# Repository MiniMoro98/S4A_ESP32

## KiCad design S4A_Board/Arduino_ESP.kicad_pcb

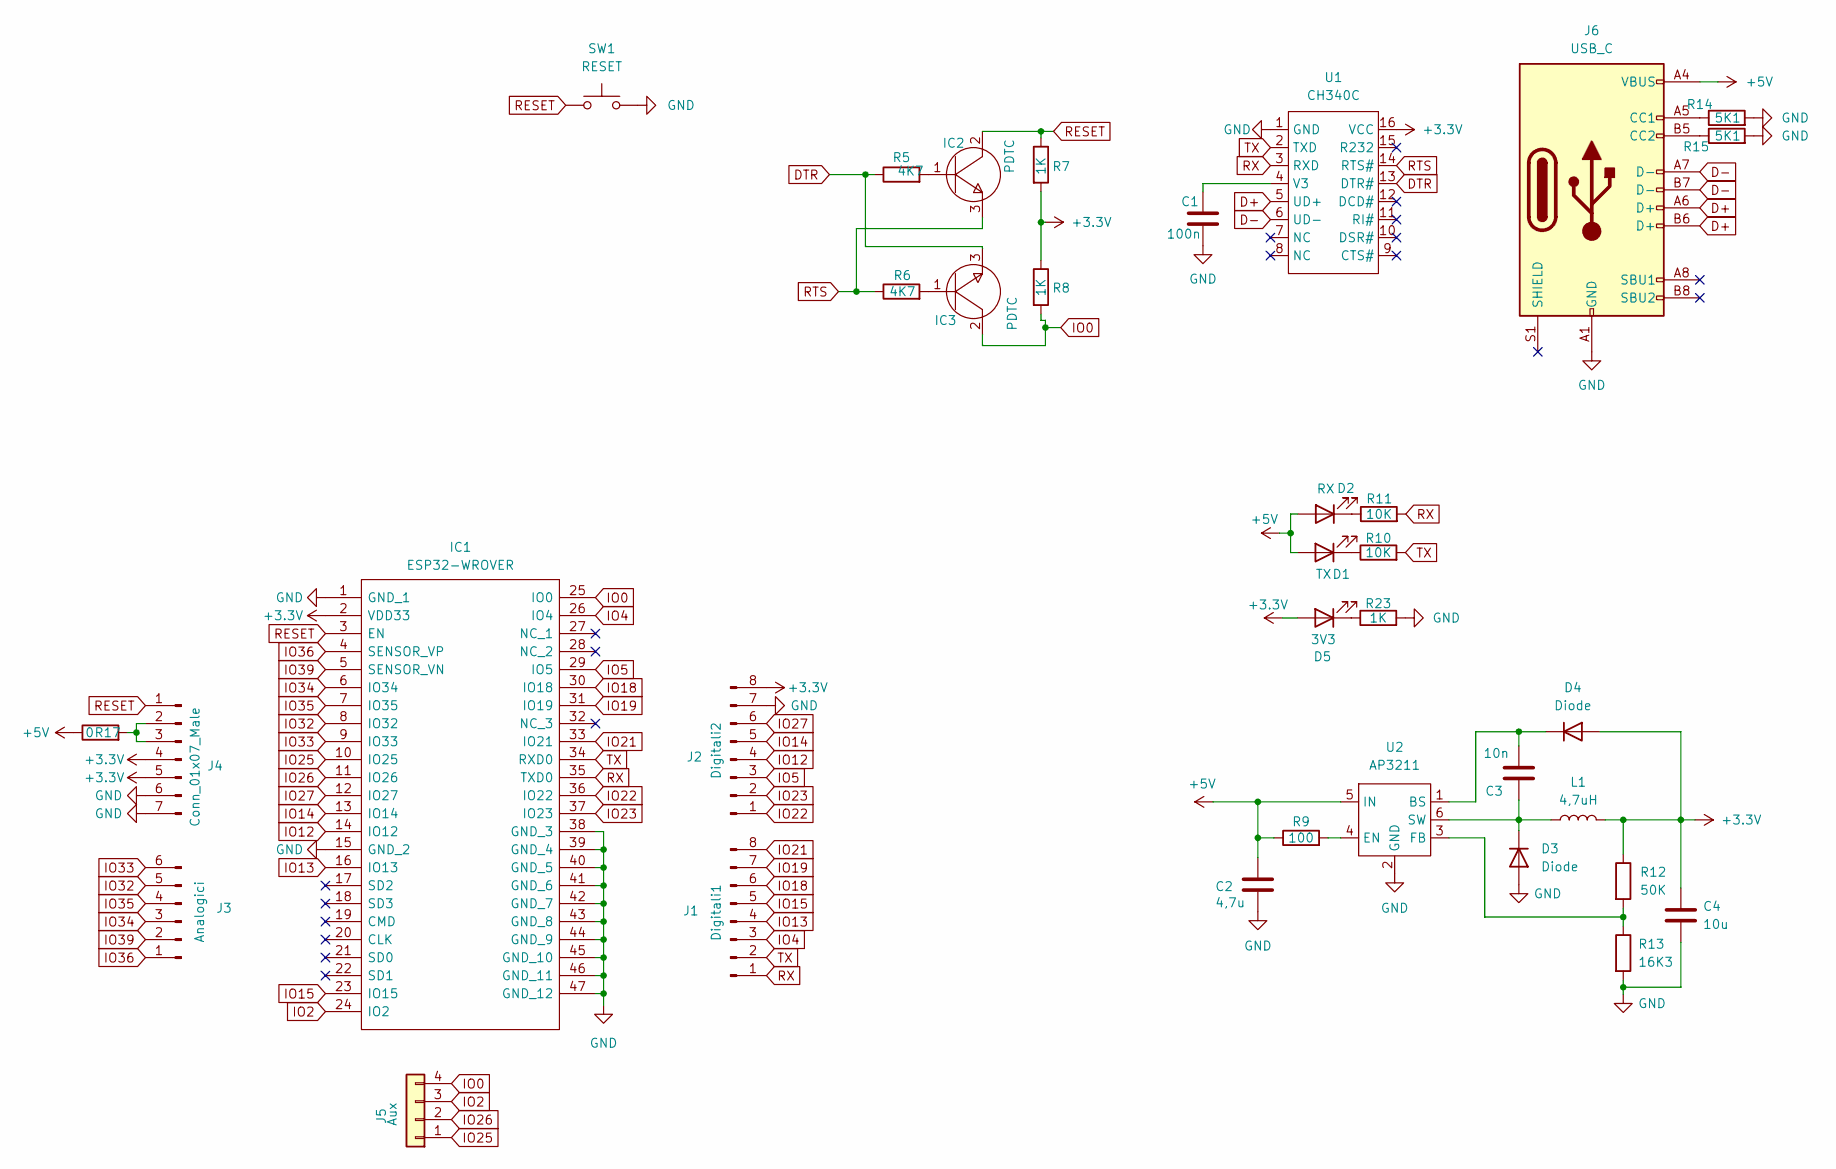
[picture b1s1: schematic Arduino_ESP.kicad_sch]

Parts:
C1: 100n; C_0603_1608Metric
C2: 4,7u; Condensatore_G
C3: 10n; Condensatore_P
C4: 10u; Condensatore_G
D1: TX; LED_0805_2012Metric
D2: RX; LED_0805_2012Metric
D3: Diode; Diodo_G
D4: Diode; Diodo_P
D5: 3V3; LED_0805_2012Metric
IC1: ESP32-WROVER; ESP32WROVERB8MB; Manufacturer_Part_Number ESP32-WROVER-B (8MB); Mouser Part Number 356-ESP32-WRO-B(8MB)
IC2, IC3: PDTC; SOT-23
J1: Digitali1; PinSocket_1x08_P2.54mm_Vertical
J2: Digitali2; PinSocket_1x08_P2.54mm_Vertical
J3: Analogici; PinSocket_1x06_P2.54mm_Vertical
J4: Conn_01x07_Male; PinSocket_1x07_P2.54mm_Vertical
J5: Aux; PinHeader_1x04_P2.54mm_Vertical
J6: USB_C; USB_C_Receptacle_HRO_TYPE-C-31-M-12
L1: 4,7uH; Induttanza
R5, R6: 4K7; R_0603_1608Metric
R7, R8, R23: 1K; R_0603_1608Metric
R9: 100; Resistenza
R10, R11: 10K; R_0603_1608Metric
R12: 50K; Resistenza
R13: 16K3; Resistenza
R14, R15: 5K1; R_0603_1608Metric
R17: 0; R_0402_1005Metric
SW1: RESET; SW_SPST_CK_RS282G05A3
U1: CH340C; SO-16_3.9x9.9mm_P1.27mm
U2: AP3211

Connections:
+3.3V: C4.1, D4.1 (A), D5.2 (A), IC1.2 (VDD33), J2.8, J4.4, J4.5, L1.2, R7.2, R8.1, R12.1, U1.16 (VCC)
+5V: C2.1, D1.2 (A), D2.2 (A), J6.A4 (VBUS), J6.A9 (VBUS), J6.B4 (VBUS), J6.B9 (VBUS), R9.1, R17.1, U2.5 (IN)
D+: J6.A6 (D+), J6.B6 (D+), U1.5 (UD+)
D-: J6.A7 (D-), J6.B7 (D-), U1.6 (UD-)
DTR: IC3.3, R5.1, U1.13 (DTR#)
GND: C1.2, C2.2, C4.2, D3.1 (A), IC1.1 (GND_1), IC1.15 (GND_2), IC1.38 (GND_3), IC1.39 (GND_4), IC1.40 (GND_5), IC1.41 (GND_6), IC1.42 (GND_7), IC1.43 (GND_8), IC1.44 (GND_9), IC1.45 (GND_10), IC1.46 (GND_11), IC1.47 (GND_12), J2.7, J4.6, J4.7, J6.A1 (GND), J6.A12 (GND), J6.B1 (GND), J6.B12 (GND), R13.2, R14.2, R15.2, R23.2, SW1.2, U1.1 (GND), U2.2 (GND)
IO0: IC1.25 (IO0), IC3.2, J5.4, R8.2
IO2: IC1.24 (IO2), J5.3
IO4: IC1.26 (IO4), J1.3
IO5: IC1.29 (IO5), J2.3
IO12: IC1.14 (IO12), J2.4
IO13: IC1.16 (IO13), J1.4
IO14: IC1.13 (IO14), J2.5
IO15: IC1.23 (IO15), J1.5
IO18: IC1.30 (IO18), J1.6
IO19: IC1.31 (IO19), J1.7
IO21: IC1.33 (IO21), J1.8
IO22: IC1.36 (IO22), J2.1
IO23: IC1.37 (IO23), J2.2
IO25: IC1.10 (IO25), J5.1
IO26: IC1.11 (IO26), J5.2
IO27: IC1.12 (IO27), J2.6
IO32: IC1.8 (IO32), J3.5
IO33: IC1.9 (IO33), J3.6
IO34: IC1.6 (IO34), J3.3
IO35: IC1.7 (IO35), J3.4
IO36: IC1.4 (SENSOR_VP), J3.1
IO39: IC1.5 (SENSOR_VN), J3.2
unnamed: D1.1 (K), R10.1
unnamed: D2.1 (K), R11.1
unnamed: C3.2, D3.2 (K), L1.1, U2.6 (SW)
unnamed: C3.1, D4.2 (K), U2.1 (BS)
unnamed: D5.1 (K), R23.1
unnamed: IC2.1, R5.2
unnamed: IC3.1, R6.2
unnamed: J4.2, J4.3, R17.2
unnamed: J6.A5 (CC1), R14.1
unnamed: J6.B5 (CC2), R15.1
unnamed: C1.1, U1.4 (V3)
unnamed: R9.2, U2.4 (EN)
unnamed: R12.2, R13.1, U2.3 (FB)
RESET: IC1.3 (EN), IC2.2, J4.1, R7.1, SW1.1
RTS: IC2.3, R6.1, U1.14 (RTS#)
RX: IC1.35 (TXD0), J1.1, R11.2, U1.3 (RXD)
TX: IC1.34 (RXD0), J1.2, R10.2, U1.2 (TXD)

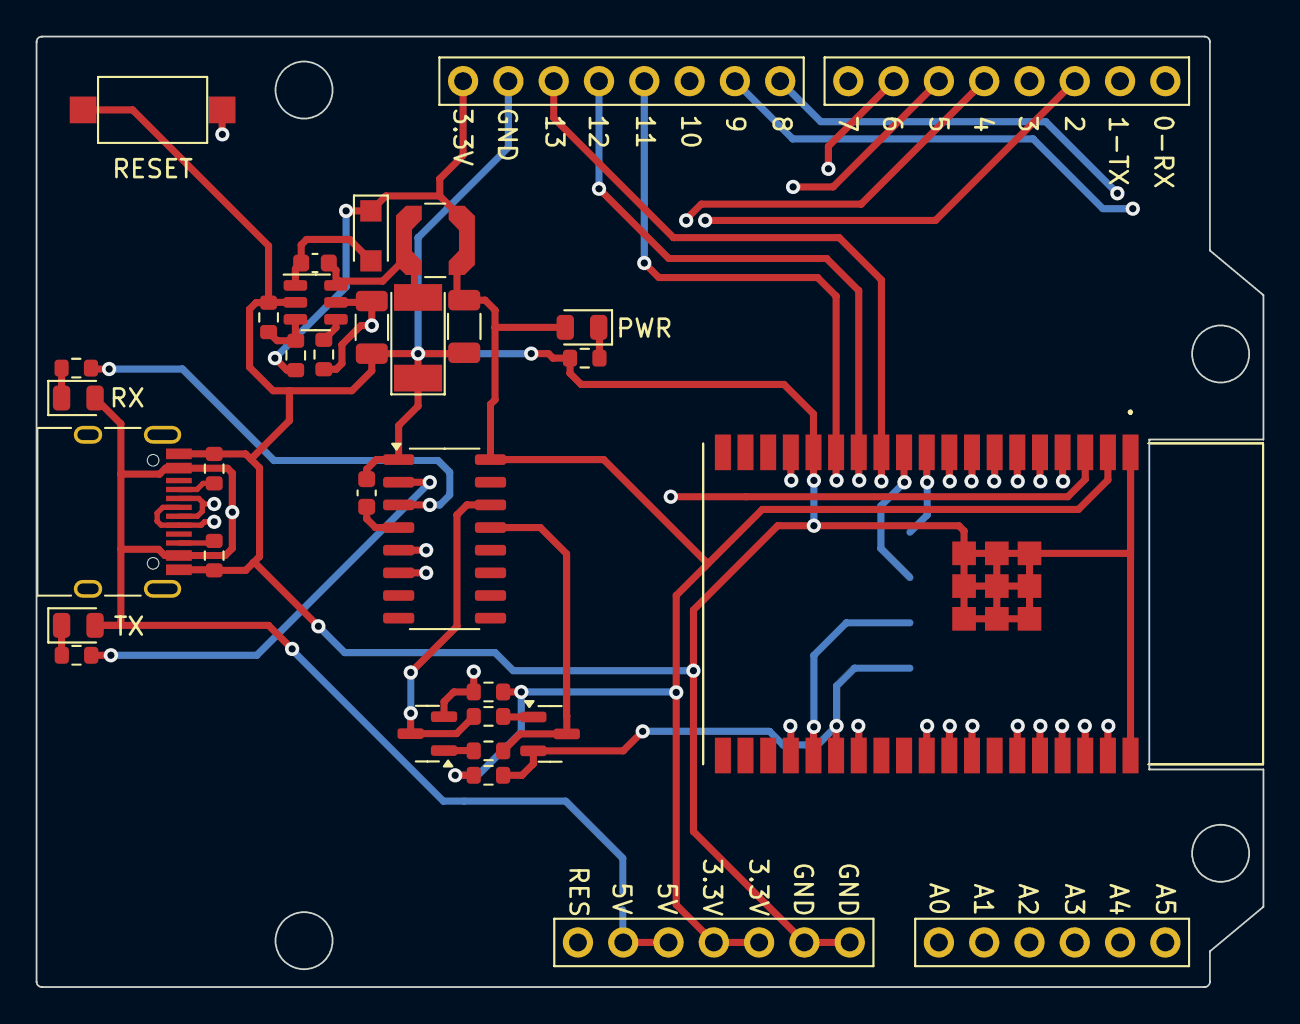
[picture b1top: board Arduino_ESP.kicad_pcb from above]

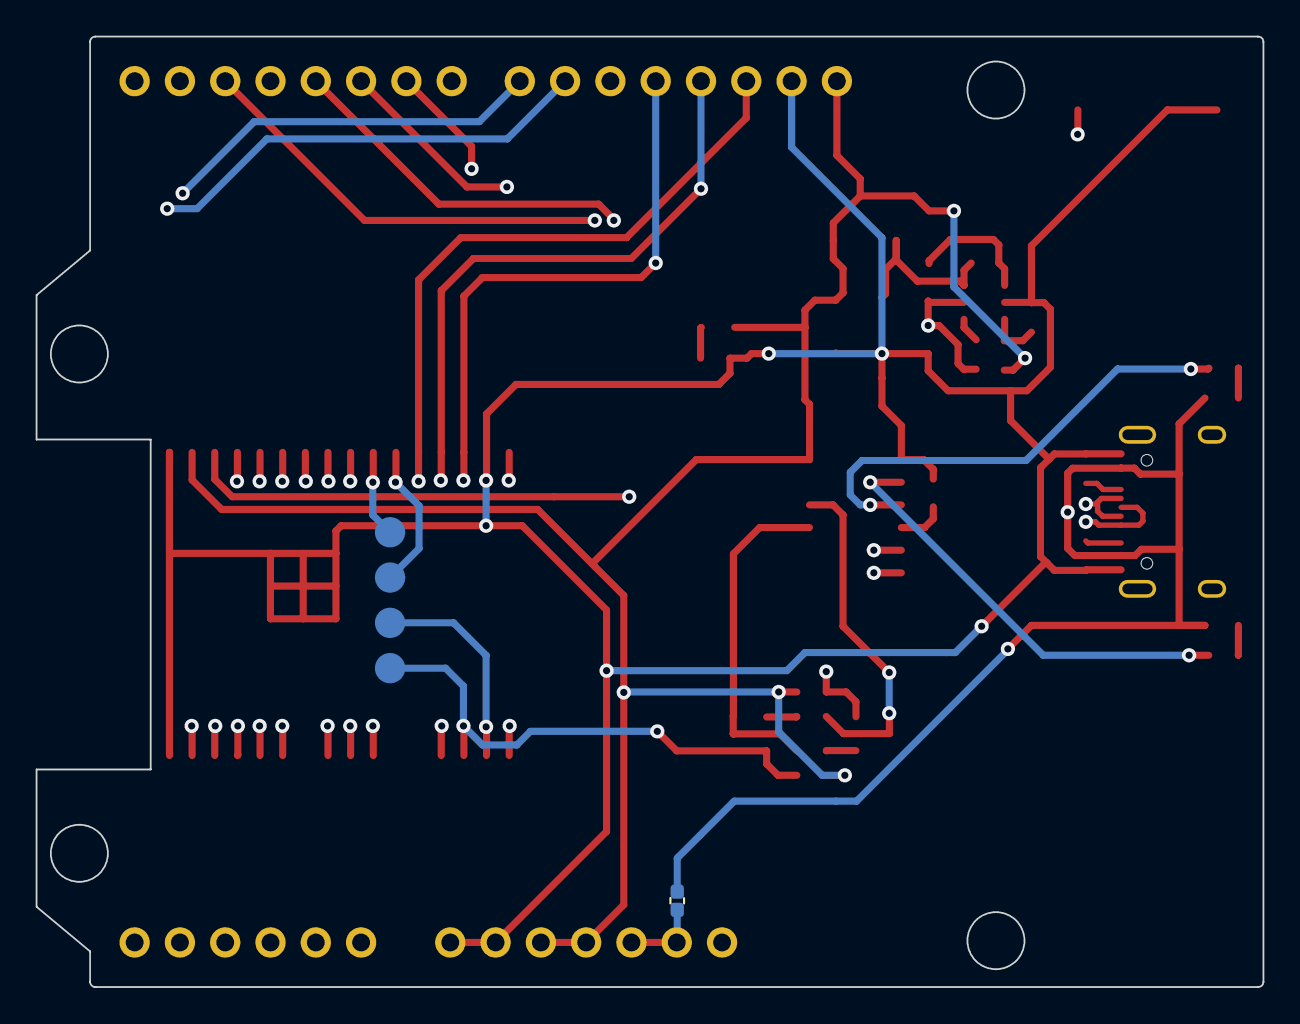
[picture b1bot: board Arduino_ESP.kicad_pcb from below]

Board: 4 copper layers, 68.8 x 53.3 mm, 35 parts (2 on the bottom side), 45 nets.

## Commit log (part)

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2024-11-27 caricamento
2024-11-27 correzione
2025-03-08 aggiornamenti
2025-03-13 Rimossi backup
